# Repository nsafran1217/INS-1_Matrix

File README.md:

# INS-1_Matrix
Matrix Display made with INS-1 Nixie Tube indicators

More info at: https://nsafran.com/ins-1-nixie-tube-matrix.html

ArduinoLibrary contains the library to use the matrix. A description of the animation data format is provided in the docs folder.

INS-1_MatrixDesigner contains a c# WinForms app to help design animations for the display. You can save and load animations from JSON files with this app. This is not a polished application and it may crash if you do something I didn't think of.
You will just copy and paste the array definition from the output text box into your Arduino code.

INS-1 Matrix Board directory contains the KiCAD files as designed. I recommend moving the resistors for the indicators away from the plated through hole. When I had the boards assembled by JLCPCB, the hole was filled with solder. I had to suck the solder out of all the holes that had the resistors right next to the anode hole.

# Completed Boards working

# Unpopulated Board

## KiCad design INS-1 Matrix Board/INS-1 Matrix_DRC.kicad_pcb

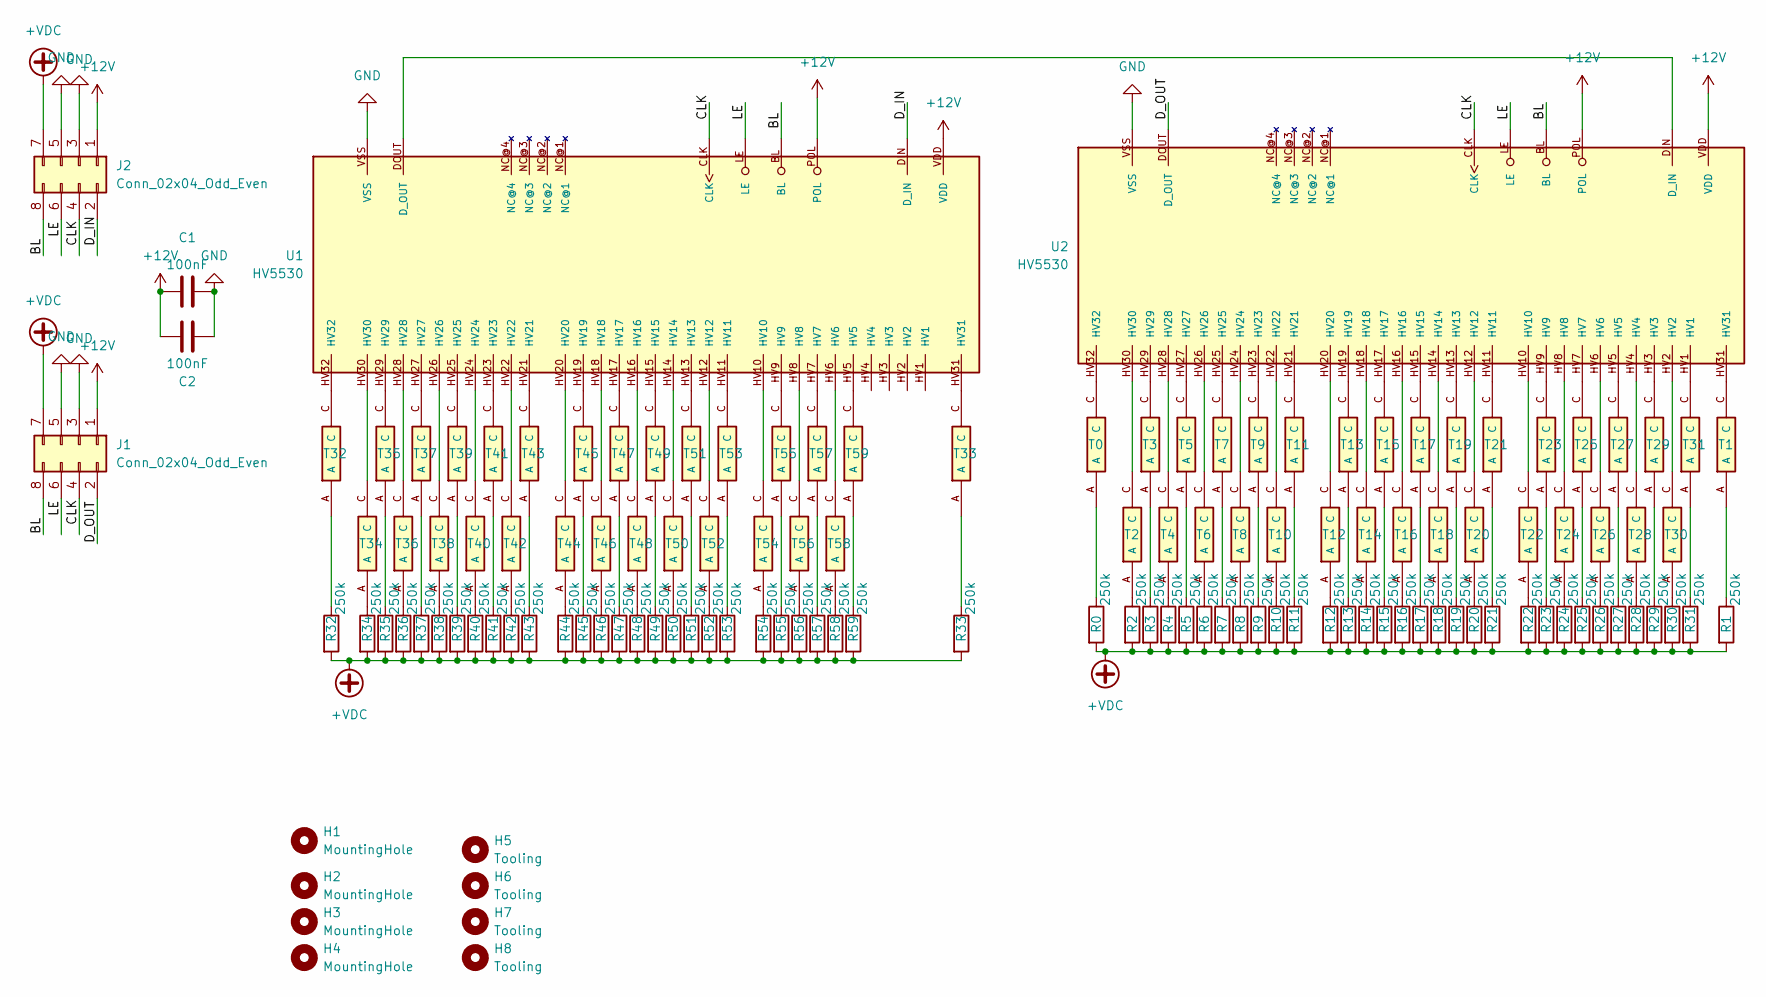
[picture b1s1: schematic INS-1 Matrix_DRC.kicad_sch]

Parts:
C1, C2: 100nF; C_0805_2012Metric_Pad1.18x1.45mm_HandSolder; LCSC C49678
H1, H2, H3, H4: MountingHole; MountingHole_3.2mm_M3
H5, H6, H7, H8: Tooling; MountingHole_1.152mm
J1, J2: Conn_02x04_Odd_Even; IDC-Header_2x04_P2.54mm_Vertical
R0, R1, R2, R3, R4, R5, R6, R7, R8, R9, R10, R11, R12, R13, R14, R15, R16, R17, R18, R19, R20, R21, R22, R23, R24, R25, R26, R27, R28, R29, R30, R31, R32, R33, R34, R35, R36, R37, R38, R39, R40, R41, R42, R43, R44, R45, R46, R47, R48, R49, R50, R51, R52, R53, R54, R55, R56, R57, R58, R59: 250k; R_0805_2012Metric_Pad1.20x1.40mm_HandSolder; LCSC C5156563
T0, T1, T2, T3, T4, T5, T6, T7, T8, T9, T10, T11, T12, T13, T14, T15, T16, T17, T18, T19, T20, T21, T22, T23, T24, T25, T26, T27, T28, T29, T30, T31, T32, T33, T34, T35, T36, T37, T38, T39, T40, T41, T42, T43, T44, T45, T46, T47, T48, T49, T50, T51, T52, T53, T54, T55, T56, T57, T58, T59: INS-1
U1, U2: HV5530; 44_PQFP_CORRECTED

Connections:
+12V: C1.1, C2.1, J1.1, J2.1, U1.POL, U1.VDD, U2.POL, U2.VDD
+VDC: J1.7, J2.7, R0.2, R1.2, R2.2, R3.2, R4.2, R5.2, R6.2, R7.2, R8.2, R9.2, R10.2, R11.2, R12.2, R13.2, R14.2, R15.2, R16.2, R17.2, R18.2, R19.2, R20.2, R21.2, R22.2, R23.2, R24.2, R25.2, R26.2, R27.2, R28.2, R29.2, R30.2, R31.2, R32.2, R33.2, R34.2, R35.2, R36.2, R37.2, R38.2, R39.2, R40.2, R41.2, R42.2, R43.2, R44.2, R45.2, R46.2, R47.2, R48.2, R49.2, R50.2, R51.2, R52.2, R53.2, R54.2, R55.2, R56.2, R57.2, R58.2, R59.2
/BL: J1.8, J2.8, U1.BL, U2.BL
/CLK: J1.4, J2.4, U1.CLK, U2.CLK
/D_IN: J2.2, U1.DIN (D_IN)
/D_OUT: J1.2, U2.DOUT (D_OUT)
/LE: J1.6, J2.6, U1.LE, U2.LE
GND: C1.2, C2.2, J1.3, J1.5, J2.3, J2.5, U1.VSS, U2.VSS
unnamed: R0.1, T0.A
unnamed: R1.1, T1.A
unnamed: R2.1, T2.A
unnamed: R3.1, T3.A
unnamed: R4.1, T4.A
unnamed: R5.1, T5.A
unnamed: R6.1, T6.A
unnamed: R7.1, T7.A
unnamed: R8.1, T8.A
unnamed: R9.1, T9.A
unnamed: R10.1, T10.A
unnamed: R11.1, T11.A
unnamed: R12.1, T12.A
unnamed: R13.1, T13.A
unnamed: R14.1, T14.A
unnamed: R15.1, T15.A
unnamed: R16.1, T16.A
unnamed: R17.1, T17.A
unnamed: R18.1, T18.A
unnamed: R19.1, T19.A
unnamed: R20.1, T20.A
unnamed: R21.1, T21.A
unnamed: R22.1, T22.A
unnamed: R23.1, T23.A
unnamed: R24.1, T24.A
unnamed: R25.1, T25.A
unnamed: R26.1, T26.A
unnamed: R27.1, T27.A
unnamed: R28.1, T28.A
unnamed: R29.1, T29.A
unnamed: R30.1, T30.A
unnamed: R31.1, T31.A
unnamed: R32.1, T32.A
unnamed: R33.1, T33.A
unnamed: R34.1, T34.A
unnamed: R35.1, T35.A
unnamed: R36.1, T36.A
unnamed: R37.1, T37.A
unnamed: R38.1, T38.A
unnamed: R39.1, T39.A
unnamed: R40.1, T40.A
unnamed: R41.1, T41.A
unnamed: R42.1, T42.A
unnamed: R43.1, T43.A
unnamed: R44.1, T44.A
unnamed: R45.1, T45.A
unnamed: R46.1, T46.A
unnamed: R47.1, T47.A
unnamed: R48.1, T48.A
unnamed: R49.1, T49.A
unnamed: R50.1, T50.A
unnamed: R51.1, T51.A
unnamed: R52.1, T52.A
unnamed: R53.1, T53.A
unnamed: R54.1, T54.A
unnamed: R55.1, T55.A
unnamed: R56.1, T56.A
unnamed: R57.1, T57.A
unnamed: R58.1, T58.A
unnamed: R59.1, T59.A
unnamed: T0.C, U2.HV32
unnamed: T1.C, U2.HV31
unnamed: T2.C, U2.HV30
unnamed: T3.C, U2.HV29
unnamed: T4.C, U2.HV28
unnamed: T5.C, U2.HV27
unnamed: T6.C, U2.HV26
unnamed: T7.C, U2.HV25
unnamed: T8.C, U2.HV24
unnamed: T9.C, U2.HV23
unnamed: T10.C, U2.HV22
unnamed: T11.C, U2.HV21
unnamed: T12.C, U2.HV20
unnamed: T13.C, U2.HV19
unnamed: T14.C, U2.HV18
unnamed: T15.C, U2.HV17
unnamed: T16.C, U2.HV16
unnamed: T17.C, U2.HV15
unnamed: T18.C, U2.HV14
unnamed: T19.C, U2.HV13
unnamed: T20.C, U2.HV12
unnamed: T21.C, U2.HV11
unnamed: T22.C, U2.HV10
unnamed: T23.C, U2.HV9
unnamed: T24.C, U2.HV8
unnamed: T25.C, U2.HV7
unnamed: T26.C, U2.HV6
unnamed: T27.C, U2.HV5
unnamed: T28.C, U2.HV4
unnamed: T29.C, U2.HV3
unnamed: T30.C, U2.HV2
unnamed: T31.C, U2.HV1
unnamed: T32.C, U1.HV32
unnamed: T33.C, U1.HV31
unnamed: T34.C, U1.HV30
unnamed: T35.C, U1.HV29
unnamed: T36.C, U1.HV28
unnamed: T37.C, U1.HV27
unnamed: T38.C, U1.HV26
unnamed: T39.C, U1.HV25
unnamed: T40.C, U1.HV24
unnamed: T41.C, U1.HV23
unnamed: T42.C, U1.HV22
unnamed: T43.C, U1.HV21
unnamed: T44.C, U1.HV20
unnamed: T45.C, U1.HV19
unnamed: T46.C, U1.HV18
unnamed: T47.C, U1.HV17
unnamed: T48.C, U1.HV16
unnamed: T49.C, U1.HV15
unnamed: T50.C, U1.HV14
unnamed: T51.C, U1.HV13
unnamed: T52.C, U1.HV12
unnamed: T53.C, U1.HV11
unnamed: T54.C, U1.HV10
unnamed: T55.C, U1.HV9
unnamed: T56.C, U1.HV8
unnamed: T57.C, U1.HV7
unnamed: T58.C, U1.HV6
unnamed: T59.C, U1.HV5
unnamed: U1.DOUT (D_OUT), U2.DIN (D_IN)

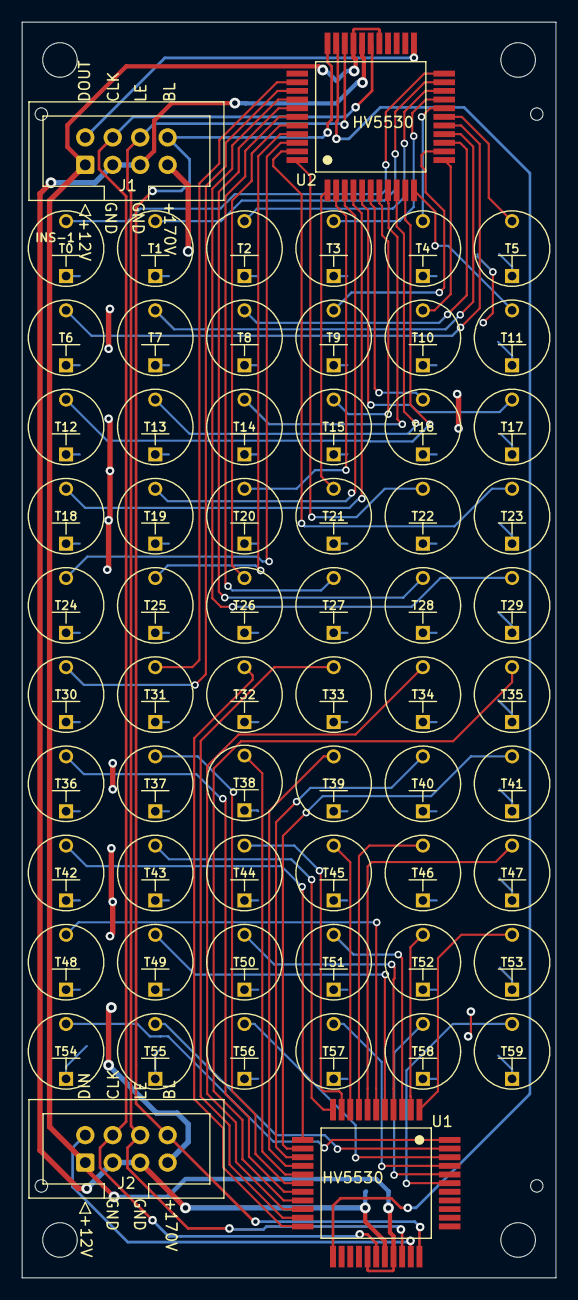
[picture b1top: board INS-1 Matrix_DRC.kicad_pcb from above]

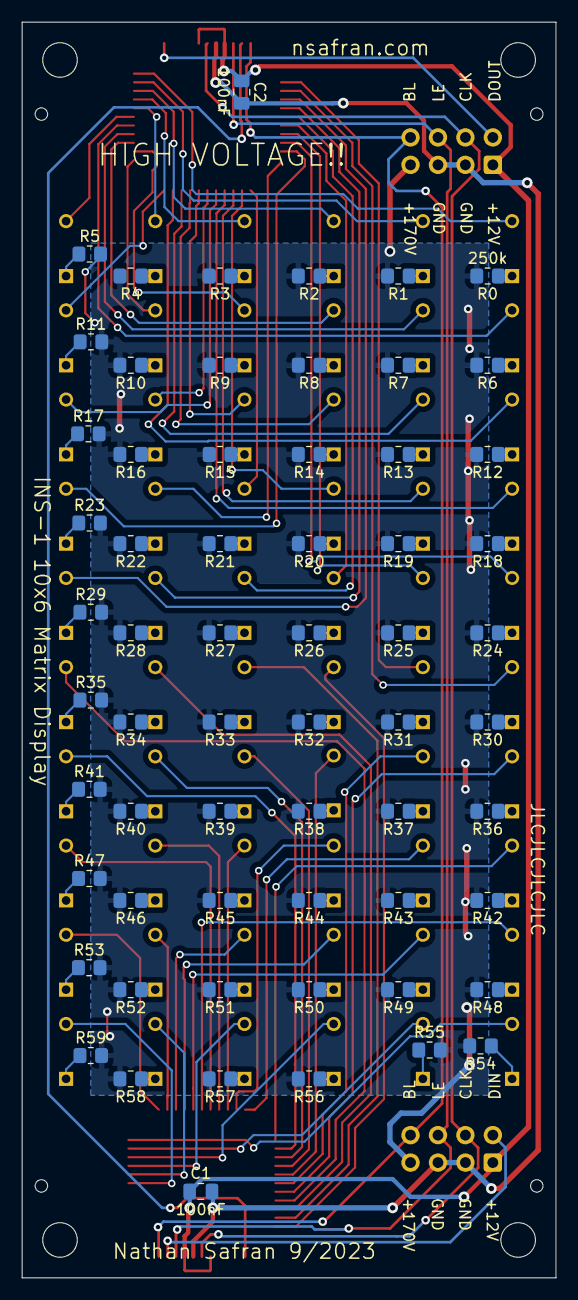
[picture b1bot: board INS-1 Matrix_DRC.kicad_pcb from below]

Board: 2 copper layers, 49.4 x 116.2 mm, 134 parts (62 on the bottom side), 129 nets.

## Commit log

2023-09-08 Init commit with Board
2023-09-08 Init Commit
2023-09-09 failing at passing 2d arrays
2023-09-09 Move back to standard arrays that just hold all the frames
2023-09-09 remove serial debugging
2023-09-09 Change to have info about animation in data
2023-09-09 Change to have animation info in data
2023-09-09 fixing unstaged changes
2023-09-11 invert data, change some data types
2023-09-20 Set blank pin so display comes on
2023-09-20 Add test sketch
2023-09-22 add delay to clock to account for slow transistors doing level shift
2023-10-15 Add matrix designer app
2023-12-04 Change POL pin to connect to 12V
2023-12-04 remove double inversion since board is fixed
2024-01-01 Fix some designer crashing bugs
